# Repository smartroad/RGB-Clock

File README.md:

# RGB Clock

See Wiki

https://github.com/smartroad/RGB-Clock/wiki/

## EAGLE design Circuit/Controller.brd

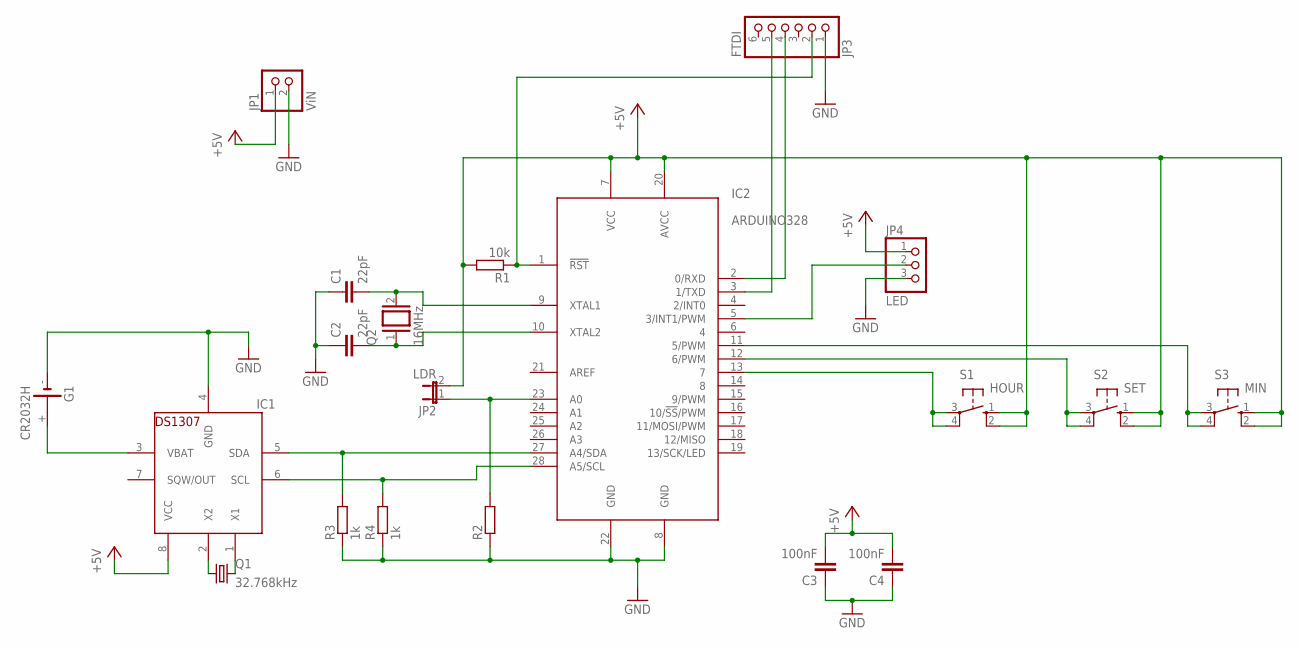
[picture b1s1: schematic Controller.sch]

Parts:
C1, C2: 22pF; C025-024X044
C3, C4: 100nF; C025-024X044
G1: CR2032H
IC1: DS1307; DIL08
IC2: ARDUINO328; DIP28
JP1: ViN; 1X02
JP2: LDR; JP1
JP3: FTDI; 1X06
JP4: LED; 1X03
Q1: 32.768kHz; TC26V
Q2: 16MHz; QS
R1: 10k; 0204/5
R2: R-EU_0204/5; 0204/5
R3, R4: 1k; 0204/5
S1: HOUR; B3F-10XX
S2: SET; B3F-10XX
S3: MIN; B3F-10XX

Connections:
+5V: C3.2, C4.2, IC1.8 (VCC), IC2.7 (VCC), IC2.20 (AVCC), JP1.1, JP2.2, JP4.1, R1.2, S1.1 (S), S1.2 (S1), S2.1 (S), S2.2 (S1), S3.1 (S), S3.2 (S1)
GND: C1.1, C2.1, C3.1, C4.1, G1.-, IC1.4 (GND), IC2.8 (GND), IC2.22 (GND), JP1.2, JP3.1, JP4.3, R2.1, R3.1, R4.1
unnamed: C1.2, IC2.9 (XTAL1), Q2.2
unnamed: C2.2, IC2.10 (XTAL2), Q2.1
unnamed: IC2.1 (!RST), JP3.2, R1.1
unnamed: IC1.5 (SDA), IC2.27 (A4/SDA), R3.2
unnamed: IC1.6 (SCL), IC2.28 (A5/SCL), R4.2
unnamed: IC2.23 (A0), JP2.1, R2.2
unnamed: IC1.2 (X2), Q1.1
unnamed: IC1.1 (X1), Q1.2
unnamed: IC2.11 (5/PWM), S3.3, S3.4 (P1)
unnamed: IC2.12 (6/PWM), S2.3, S2.4 (P1)
unnamed: IC2.13 (7), S1.3, S1.4 (P1)
unnamed: IC2.2 (0/RXD), JP3.4
unnamed: IC2.3 (1/TXD), JP3.5
unnamed: IC2.5 (3/INT1/PWM), JP4.2
VBAT: G1.+, IC1.3 (VBAT)

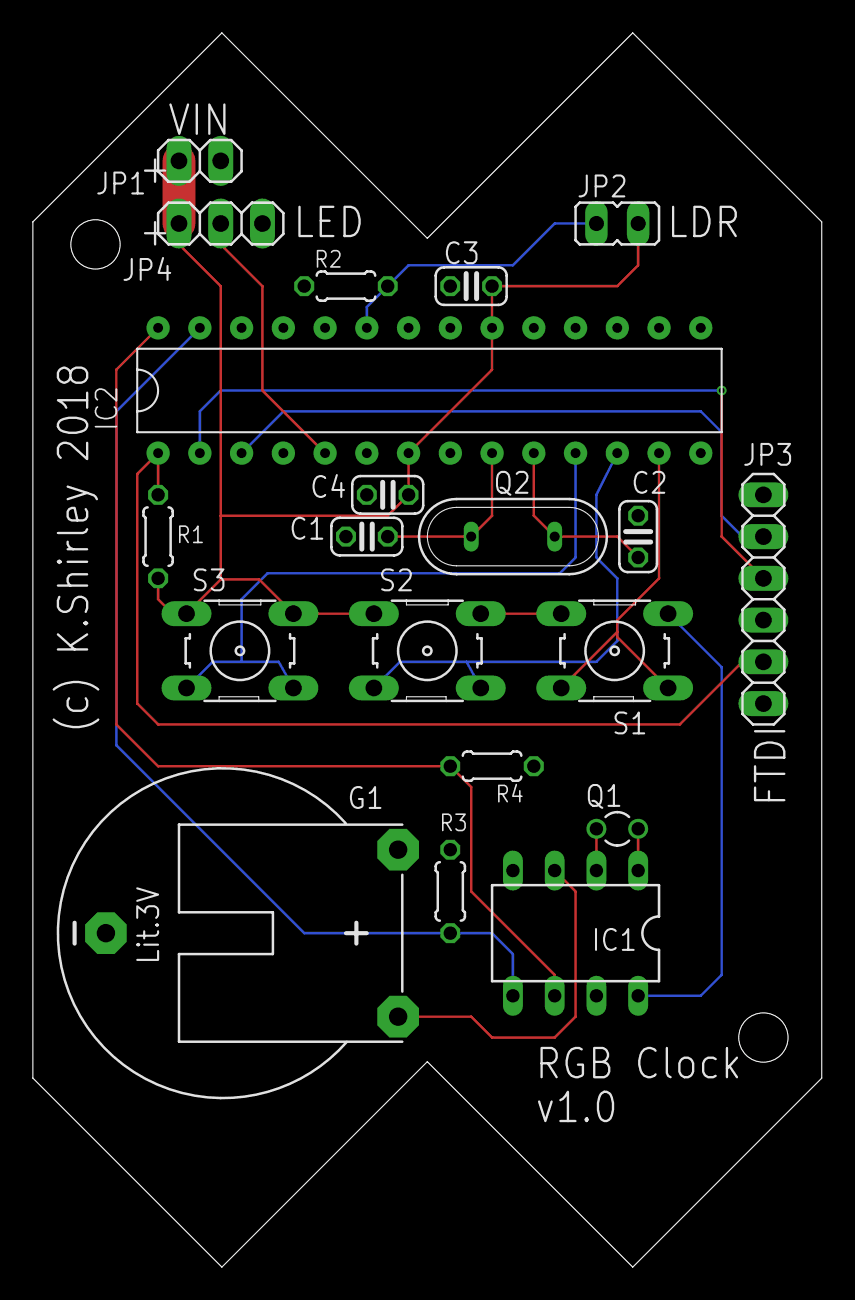
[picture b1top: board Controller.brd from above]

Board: 2 copper layers, 48.0 x 75.1 mm, 20 parts (0 on the bottom side), 17 nets.

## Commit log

2017-12-27 Initial Upload
2017-12-28 DST and diagnostics
    Added in a diagnostic that switches all the LED's between red, green and blue with a 5 second delay to test LEDs. Operate by holding the hour button when powering on.
    When setting DST the display will now show "on" and "of"f when setting.
2018-01-07 Display Timer
    updated to be able to turn off display between a given time.
2018-01-11 Change display for setting On/Off times for clock
2018-01-11 Corrected asuto on/off so works if off time is less than the on time
2018-01-13 Update to 3D file
2018-01-23 Stop blocking
    Stopped blocking on setting the automatic switch on brightness level. Tidied some of the setup code to make it easier to get into admin modes
2018-01-27 Additional mode
    Added option to have display off by setting auto on/off times to both be 0 (midnight). Display will now stay off until light level reaches the auto amount - or just stay off if auto is off.
2018-01-27 Changed burn in test
    Bur in test will now allow manual setting of colour between white, red, green or blue. Display will stay on chosen colour until changed. Display will not go into clock mode - power cycle needed to sh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
2018-01-27 Only update time/EEPROM on change
    only update the clock or EEPROM when a change has happened. Saves seconds being reset to 0 if just wanting to get to DST or other settings and excessive EEPROM writes.
2018-01-27 ASCII subset
    updated the numbers array to include all possible letters that are possible with a 7 segment display - missing KMVWXZ as not possible to display
2018-01-27 Revert "ASCII subset"
    This reverts commit 2bfa0c480bc69c3aae92d0a1ce3b716ec8d72677.
2018-01-27 ASCII into FLASH
    Updated numbers array to reside in progmem and also contain a subset of ASCII. Uppercase only and not all characters are possible KMVWXZ. showDigit has been updated, allowing either a CHAR or 0-9 dig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
2018-01-27 Clear EEPROM
    option on bootup to clear EEPROM
2018-01-27 Clear EEPROM
    only read EEPROM after clear to prevent update of clock colour
2018-01-28 12/24 and leading Zero
    Now able to set 12 hour mode (setting will always be 24hr) and set a leading zero from the hour display
2018-01-30 AM/PM Correction
    AM indicator was not showing correctly (forgot the equals sign haha)
2018-02-04 Standalone circuit
    Uploaded V0.1 of the custom circuit for the board. Boards have been ordered and this will be updated once testing has been done if needed.
